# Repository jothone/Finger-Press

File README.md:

### Cuantificación de fuerza e individuación digital en rehabilitación de mano post-ACV
# Finger-Press
Dispositivo interactivo para la rehabilitación y evaluación de la fuerza de los dedos en pacientes post-ACV

1. Descripción del proyecto

Finger-Press es un proyecto de desarrollo tecnológico que busca diseñar e implementar un dispositivo electrónico para apoyar la rehabilitación de la mano en pacientes que han sufrido un accidente cerebrovascular (ACV).

El dispositivo consiste en un piano en miniatura, fabricado mediante impresión 3D, que incorpora sensores de fuerza (FSR) en cada una de sus cinco teclas, permitiendo medir de manera independiente la fuerza ejercida por cada dedo.

El sistema contará con luces LED que se encenderán siguiendo secuencias de activación, indicando al usuario qué tecla debe presionar. Durante cada ejercicio, se registrará la fuerza aplicada en la tecla indicada y se evaluará si existe presión involuntaria sobre las demás teclas.

Además, se incorporarán estímulos sonoros asociados a las pulsaciones, con el propósito de desarrollar una experiencia interactiva y didáctica que favorezca la participación del paciente durante los ejercicios.

2. Objetivo general del proyecto
Diseñar e implementar un prototipo electrónico interactivo capaz de medir, registrar y visualizar de manera independiente la fuerza ejercida por los dedos durante ejercicios guiados de pulsación, con el propósito de apoyar la evaluación y rehabilitación funcional de la mano en pacientes post-ACV.

3. Objetivos especificos del proyecto
* Medir la fuerza ejercida por cada dedo mediante sensores FSR.
* Registrar la fuerza instantánea y máxima alcanzada durante los ejercicios.
* Detectar posibles activaciones involuntarias de otros dedos durante una pulsación dirigida.
* Implementar una secuencia de luces LED que indique al usuario qué tecla debe presionar.
* Incorporar estímulos sonoros para desarrollar una experiencia interactiva.
* Visualizar los resultados obtenidos durante cada sesión para evaluar el desempeño del usuario.

4. ¿Cómo buscamos que funcione el dispositivo?
* El sistema enciende una luz LED que indica qué tecla debe presionar el paciente (post_ACV).
* El usuario identifica la tecla y la presiona con el dedo correspondiente.
* El sensor FSR registra la presión ejercida sobre la tecla.
* El microcontrolador procesa las señales de los sensores y determina la fuerza aplicada.
* El sistema registra simultáneamente las señales de las demás teclas para identificar posibles activaciones involuntarias.
* Se genera una respuesta sonora asociada a la pulsación.
* Los resultados se registran y visualizan mediante una interfaz para evaluar el desempeño durante la sesión.

5. Componentes principales
* Cinco sensores de fuerza FSR.
* Microcontrolador para adquisición y procesamiento de señales.
* Luces LED para indicar las teclas objetivo.
* Buzzer
* Resistencias
* Estructura mecánica de piano en miniatura fabricada mediante impresión 3D.
* Interfaz de visualización de resultados.

6. ¿En qué parte del proyecto estamos?
Estamos en el proceso de desarrollar la placa y poder empezar a incorporar los elementos elctrciso. Además, estamos tomando en consideración las modificaciones que han surgido a lo largo del proceso.

7. Conclusión
Finalmente, Finger-Press es prototipo orientado a complementar las herramientas de evaluación y rehabilitación de la mano para pacientes post-ACV.

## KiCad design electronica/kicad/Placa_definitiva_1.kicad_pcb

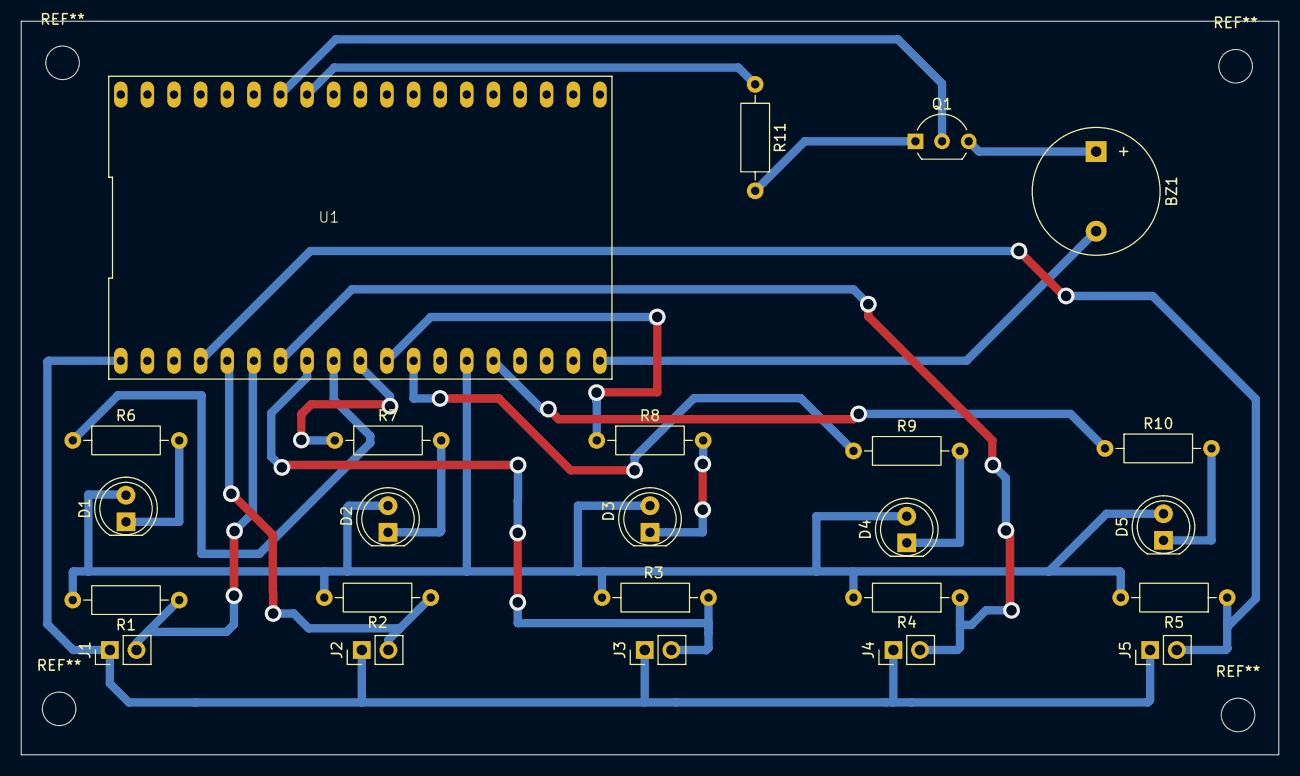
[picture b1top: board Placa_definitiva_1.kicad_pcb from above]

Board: 2 copper layers, 120.0 x 70.0 mm, 24 parts (0 on the bottom side), 20 nets.

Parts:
BZ1: Buzzer; Buzzer_12x9.5RM7.6
D1, D2, D3, D4, D5: LED; LED_D5.0mm
J1, J2, J3, J4, J5: conec.; PinHeader_1x02_P2.54mm_Vertical
Q1: Q_NPN; TO-92L_Inline_Wide
R1, R2, R3, R4, R5: 10k; R_Axial_DIN0207_L6.3mm_D2.5mm_P10.16mm_Horizontal
R6, R7, R8, R9, R10: 300; R_Axial_DIN0207_L6.3mm_D2.5mm_P10.16mm_Horizontal
R11: 1k; R_Axial_DIN0207_L6.3mm_D2.5mm_P10.16mm_Horizontal
U1: ESP32-WROOM-32; ESP32-DevKitC-V4

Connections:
+3V3: J1.1, J2.1, J3.1, J4.1, J5.1, U1.2 (VDD)
/Buzzer: R11.1, U1.31 (IO19)
/Fsr_1: J1.2, R1.1, U1.7 (IO35)
/Fsr_2: J2.2, R2.1, U1.6 (IO34)
/Fsr_3: J3.2, R3.1, U1.9 (IO33)
/Fsr_4: J4.2, R4.1, U1.8 (IO32)
/Fsr_5: J5.2, R5.1, U1.5 (SENSOR_VN)
/Led_1: R6.1, U1.10 (IO25)
/Led_2: R7.1, U1.11 (IO26)
/Led_3: R8.1, U1.12 (IO27)
/Led_4: R9.1, U1.13 (IO14)
GND: D1.2 (A), D2.2 (A), D3.2 (A), D4.2 (A), D5.2 (A), Q1.C, R1.2, R2.2, R3.2, R4.2, R5.2, U1.1 (GND), U1.38 (GND)
unnamed: BZ1.1 (+), Q1.E
unnamed: D1.1 (K), R6.2
unnamed: D2.1 (K), R7.2
unnamed: D3.1 (K), R8.2
unnamed: D4.1 (K), R9.2
unnamed: D5.1 (K), R10.2
unnamed: Q1.B, R11.2
unnamed: R10.1, U1.16 (IO13)
